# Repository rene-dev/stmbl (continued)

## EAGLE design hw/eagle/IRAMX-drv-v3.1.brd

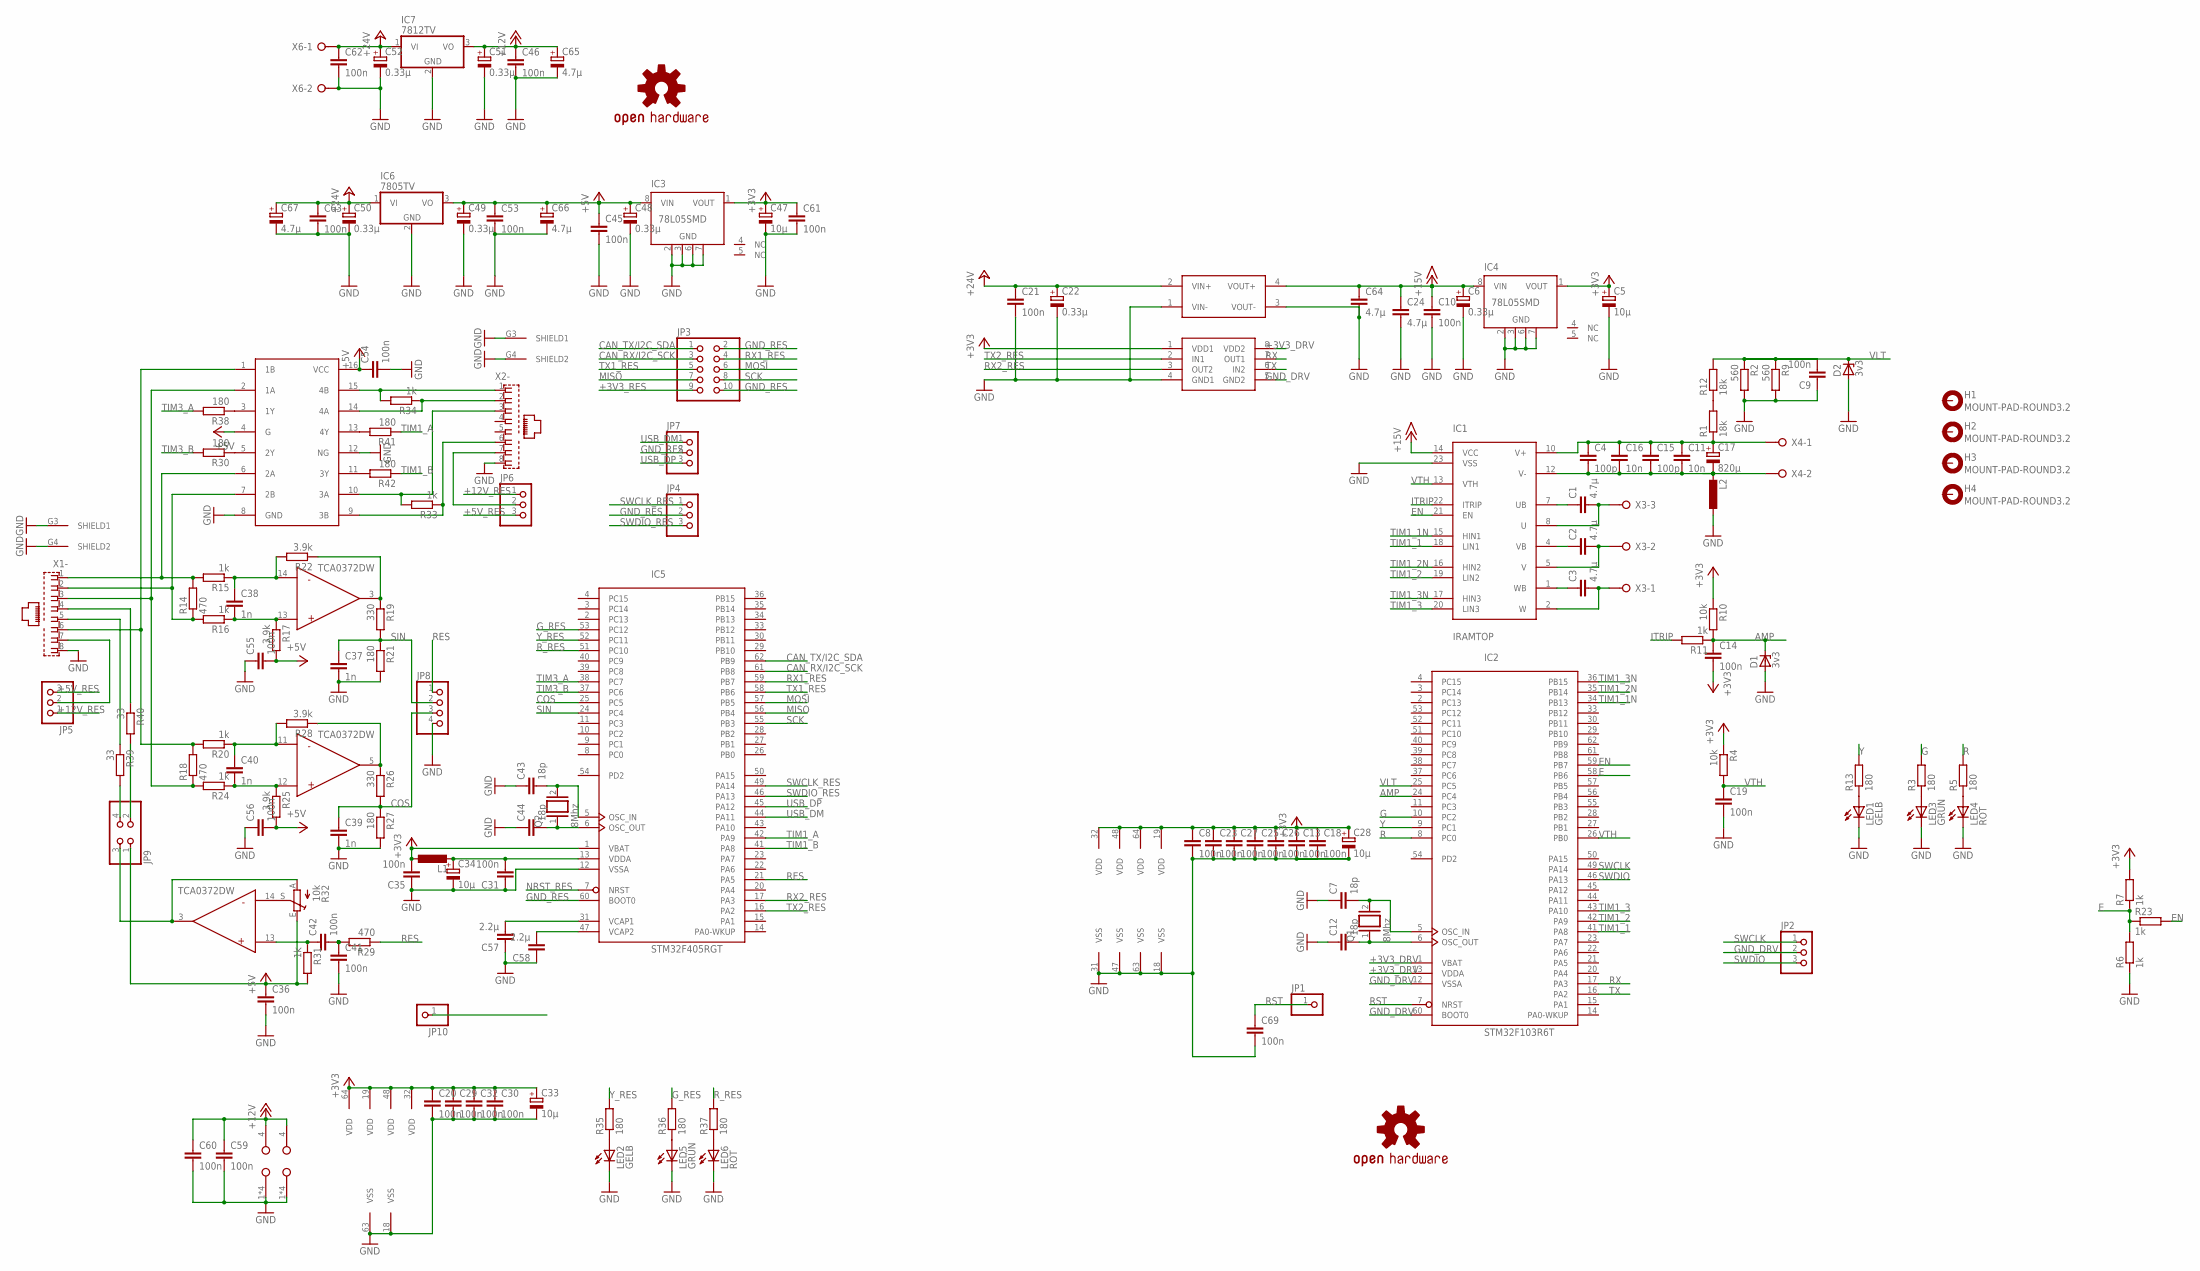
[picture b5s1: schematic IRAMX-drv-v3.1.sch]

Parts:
C1, C2, C3, C24, C64: 4.7µ; C0805K
C4, C15: 100p; C1206K
C5, C28, C33, C34, C47: 10µ; A/3216-18R
C6, C22, C48, C49, C50, C51, C52: 0.33µ; A/3216-18R
C7, C12, C43, C44: 18p; C0805
C8, C9, C10, C13, C14, C18, C19, C20, C21, C23, C25, C26, C27, C29, C30, C31, C32, C35, C36, C41, C42, C45, C46, C53, C54, C55, C56, C59, C60, C61, C62, C63, C69: 100n; C0805K
C11, C16: 10n; C0805K
C17: 820µ; EB35D
C37, C38, C39, C40: 1n; C0805K
C57, C58: 2.2µ; C0805K
C65, C66, C67: 4.7µ; E2,5-6
D1, D2: 3v3; SOD80C
H1, H2, H3, H4: MOUNT-PAD-ROUND3.2; 3,2-PAD
IC1: IRAMTOP; SIP23_TOP
IC2: STM32F103R6T; LQFP64
IC3, IC4: 78L05SMD; SO08
IC5: STM32F405RGT; LQFP64
IC6: 7805TV; TO220V
IC7: 7812TV; TO220V
JP1, JP10: PINHD-1X1; 1X01
JP2, JP4, JP5, JP6, JP7: PINHD-1X3; 1X03
JP3: PINHD-2X5; 2X05
JP8: PINHD-1X4; 1X04
JP9: PINHD-2X2; 2X02
L1, L2: L-EUL2825P; L2825P
LED1, LED2: GELB; LED3MM
LED3, LED5: GRÜN; LED3MM
LED4, LED6: ROT; LED3MM
LOGO1, LOGO2: OSHW-LOGOL; OSHW-LOGO-L
Q1, Q2: 8Mhz; QS
R1, R12: 18k; CER
R2, R9: 560; R0805
R3, R5, R13, R21, R27, R30, R35, R36, R37, R38, R41, R42: 180; R0805
R4, R10: 10k; R0805
R6, R7, R11, R15, R16, R20, R23, R24, R31, R33, R34: 1k; R0805
R14, R18, R29: 470; R0805
R17, R22, R25, R28: 3.9k; R0805
R19, R26: 330; R0805
R32: 10k; CA6V
R39, R40: 33; R0805
U$1: SI8621; SOIC08
U$2: RO-XXXX; SIP4
U$3, U$4: TCA0372DWDM2; TCA0372DM2
U$5: AM26LS32ACD; SO16
X1, X2: RJ45
X3: W237-03P; W237-133
X4, X6: W237-02P; W237-132

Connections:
+3V3_DRV: C5.+, C8.1, C13.1, C14.2, C18.1, C23.1, C25.1, C26.1, C27.1, C28.+, IC2.1 (VBAT), IC2.13 (VDDA), IC2.19 (VDD), IC2.32 (VDD), IC2.48 (VDD), IC2.64 (VDD), IC4.1 (VOUT), R4.1, R7.2, R10.1, U$1.8 (VDD2)
+3V3_RES: C20.1, C29.1, C30.1, C32.1, C33.+, C35.2, C47.+, C61.1, IC3.1 (VOUT), IC5.1 (VBAT), IC5.19 (VDD), IC5.32 (VDD), IC5.48 (VDD), IC5.64 (VDD), JP3.9, L1.1, U$1.1 (VDD1)
+5V_RES: C36.1, C45.1, C48.+, C49.+, C53.1, C54.1, C55.2, C56.2, C66.+, IC3.8 (VIN), IC6.3 (VO), JP5.3, JP6.3, JP9.1, R17.2, R25.2, R31.2, R32.E, U$5.4 (G), U$5.16 (VCC)
+12V_RES: C46.1, C51.+, C59.1, C60.1, C65.+, IC7.3 (VO), JP5.1, JP6.1, U$3.4 (VCC), U$4.4 (VCC)
+15V_DRV: C6.+, C10.1, C24.1, C64.1, IC1.14 (VCC), IC4.8 (VIN), U$2.4 (VOUT+)
+24V_RES: C21.1, C22.+, C50.+, C52.+, C62.1, C63.1, C67.+, IC6.1 (VI), IC7.1 (VI), U$2.2 (VIN+), X6.1
AMP: C14.1, D1.C, IC2.24 (PC4), R10.2, R11.1
CAN_RX/I2C_SCK: IC5.61 (PB8), JP3.3
CAN_TX/I2C_SDA: IC5.62 (PB9), JP3.1
COS: C39.1, IC5.25 (PC5), JP8.3, R26.2, R27.1
E: IC2.58 (PB6), R6.2, R7.1, R23.1
EN: IC1.21 (EN), IC2.59 (PB7), R23.2
G: IC2.10 (PC2), R3.2
GND_DRV: C5.-, C6.-, C7.1, C8.2, C9.1, C10.2, C12.1, C13.2, C18.2, C19.2, C23.2, C24.2, C25.2, C26.2, C27.2, C28.-, C64.2, C69.2, D1.A, D2.A, IC1.23 (VSS), IC2.12 (VSSA), IC2.18 (VSS), IC2.31 (VSS), IC2.47 (VSS), IC2.60 (BOOT0), IC2.63 (VSS), IC4.2 (GND), IC4.3 (GND), IC4.6 (GND), IC4.7 (GND), JP2.2, L2.1, LED1.K (C), LED3.K (C), LED4.K (C), R2.2, R6.1, R9.2, U$1.5 (GND2), U$2.3 (VOUT-)
GND_RES: C20.2, C21.2, C22.-, C29.2, C30.2, C31.1, C32.2, C33.-, C34.-, C35.1, C36.2, C37.2, C39.2, C41.2, C43.1, C44.1, C45.2, C46.2, C47.-, C48.-, C49.-, C50.-, C51.-, C52.-, C53.2, C54.2, C55.1, C56.1, C57.1, C58.1, C59.2, C60.2, C61.2, C62.2, C63.2, C65.-, C66.-, C67.-, IC3.2 (GND), IC3.3 (GND), IC3.6 (GND), IC3.7 (GND), IC5.12 (VSSA), IC5.18 (VSS), IC5.60 (BOOT0), IC5.63 (VSS), IC6.2 (GND), IC7.2 (GND), JP3.2, JP3.10, JP4.2, JP7.2, JP8.4, LED2.K (C), LED5.K (C), LED6.K (C), R21.2, R27.2, U$1.4 (GND1), U$2.1 (VIN-), U$3.1 (GND), U$3.8 (GND), U$3.9 (GND), U$3.16 (GND), U$4.1 (GND), U$4.8 (GND), U$4.9 (GND), U$4.16 (GND), U$5.8 (GND), U$5.12 (NG), X1.8, X1.G3 (SHIELD1), X1.G4 (SHIELD2), X2.8, X2.G3 (SHIELD1), X2.G4 (SHIELD2), X6.2
G_RES: IC5.53 (PC12), R36.2
ITRIP: IC1.22 (ITRIP), R11.2
MISO: IC5.56 (PB4), JP3.7
MOSI: IC5.57 (PB5), JP3.6
unnamed: C1.1, IC1.7 (UB)
unnamed: R1.P$2 (2), R12.P$1 (1)
unnamed: C2.1, IC1.4 (VB)
unnamed: LED2.A, R35.1
unnamed: C3.1, IC1.1 (WB)
unnamed: R32.S, U$4.14 (IN-)
unnamed: LED3.A, R3.1
unnamed: LED4.A, R5.1
unnamed: C7.2, IC2.5 (OSC_IN), Q1.2
unnamed: LED5.A, R36.1
unnamed: C12.2, IC2.6 (OSC_OUT), Q1.1
unnamed: C58.2, IC5.47 (VCAP2)
unnamed: C57.2, IC5.31 (VCAP1)
unnamed: C44.2, IC5.6 (OSC_OUT), Q2.1
unnamed: JP5.2, X1.7
unnamed: JP9.4, R39.2
unnamed: R19.1, R22.1, U$3.3 (OUT)
unnamed: C38.2, R16.1, R17.1, U$3.13 (IN+)
unnamed: LED6.A, R37.1
unnamed: JP9.2, R40.2
unnamed: C40.2, R24.1, R25.1, U$3.12 (IN+)
unnamed: JP6.2, X2.7
unnamed: R26.1, R28.1, U$3.5 (OUT)
unnamed: R40.1, X1.4
unnamed: C40.1, R20.1, R28.2, U$3.11 (IN-)
unnamed: R34.2, U$5.15 (4B), X2.1
unnamed: C41.1, C42.2, R29.2
unnamed: C42.1, R31.1, U$4.13 (IN+)
unnamed: C38.1, R15.1, R22.2, U$3.14 (IN-)
unnamed: JP9.3, R32.A, U$4.3 (OUT)
unnamed: R39.1, X1.5
unnamed: R30.1, U$5.5 (2Y)
unnamed: R34.1, U$5.14 (4A), X2.2
unnamed: R33.2, U$5.10 (3A), X2.3
unnamed: R33.1, U$5.9 (3B), X2.6
unnamed: C43.2, IC5.5 (OSC_IN), Q2.2
unnamed: R18.2, R20.2, U$5.1 (1B), X1.6
unnamed: R14.1, R16.2, U$5.7 (2B), X1.2
unnamed: R42.2, U$5.11 (3Y)
unnamed: LED1.A, R13.1
unnamed: R41.2, U$5.13 (4Y)
unnamed: R38.1, U$5.3 (1Y)
unnamed: C31.2, C34.+, IC5.13 (VDDA), L1.2
unnamed: R14.2, R15.2, U$5.6 (2A), X1.1
unnamed: R18.1, R24.2, U$5.2 (1A), X1.3
NRST_RES: IC5.7 (NRST), JP10.1
R: IC2.8 (PC0), R5.2
RES: IC5.21 (PA5), JP8.1, R29.1
RST: C69.1, IC2.7 (NRST), JP1.1
RX: IC2.17 (PA3), U$1.7 (OUT1)
RX1_RES: IC5.59 (PB7), JP3.4
RX2_RES: IC5.17 (PA3), U$1.3 (OUT2)
R_RES: IC5.51 (PC10), R37.2
SCK: IC5.55 (PB3), JP3.8
SIN: C37.1, IC5.24 (PC4), JP8.2, R19.2, R21.1
SWCLK: IC2.49 (PA14), JP2.1
SWCLK_RES: IC5.49 (PA14), JP4.1
SWDIO: IC2.46 (PA13), JP2.3
SWDIO_RES: IC5.46 (PA13), JP4.3
TIM1_1: IC1.18 (LIN1), IC2.41 (PA8)
TIM1_1N: IC1.15 (HIN1), IC2.34 (PB13)
TIM1_2: IC1.19 (LIN2), IC2.42 (PA9)
TIM1_2N: IC1.16 (HIN2), IC2.35 (PB14)
TIM1_3: IC1.20 (LIN3), IC2.43 (PA10)
TIM1_3N: IC1.17 (HIN3), IC2.36 (PB15)
TIM1_A: IC5.42 (PA9), R41.1
TIM1_B: IC5.41 (PA8), R42.1
TIM3_A: IC5.38 (PC7), R38.2
TIM3_B: IC5.37 (PC6), R30.2
TX: IC2.16 (PA2), U$1.6 (IN2)
TX1_RES: IC5.58 (PB6), JP3.5
TX2_RES: IC5.16 (PA2), U$1.2 (IN1)
U: C1.2, IC1.8 (U), X3.3
USB_DM: IC5.44 (PA11), JP7.1
USB_DP: IC5.45 (PA12), JP7.3
V: C2.2, IC1.5 (V), X3.2
V+: C4.1, C11.1, C15.1, C16.1, C17.+, IC1.10 (V+), R1.P$1 (1), X4.1
V-: C4.2, C11.2, C15.2, C16.2, C17.-, IC1.12 (V-), L2.2, X4.2
VLT: C9.2, D2.C, IC2.25 (PC5), R2.1, R9.1, R12.P$2 (2)
VTH: C19.1, IC1.13 (VTH), IC2.26 (PB0), R4.2
W: C3.2, IC1.2 (W), X3.1
Y: IC2.9 (PC1), R13.2
Y_RES: IC5.52 (PC11), R35.2

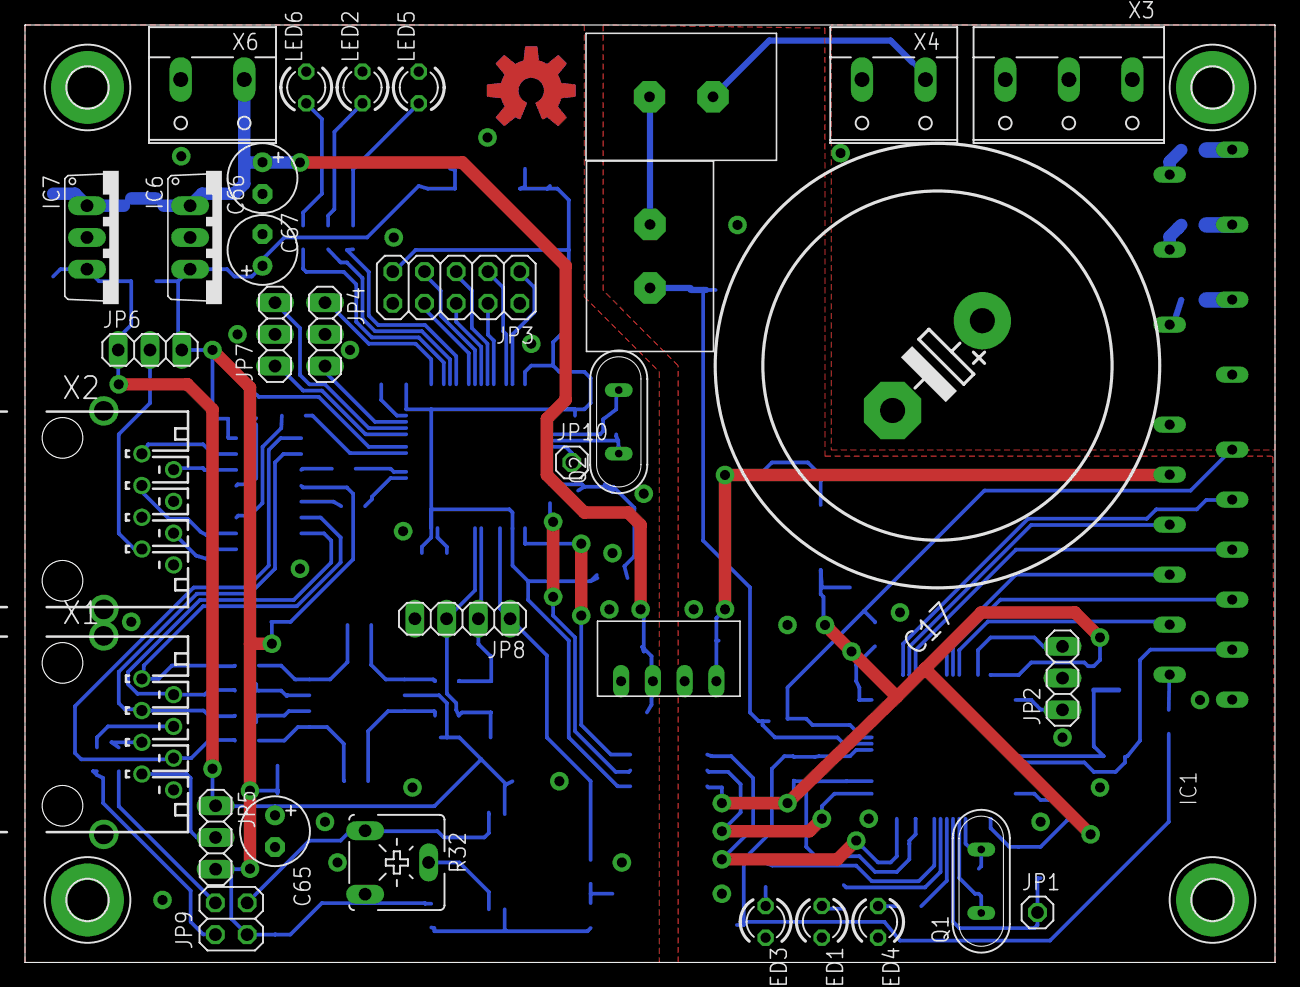
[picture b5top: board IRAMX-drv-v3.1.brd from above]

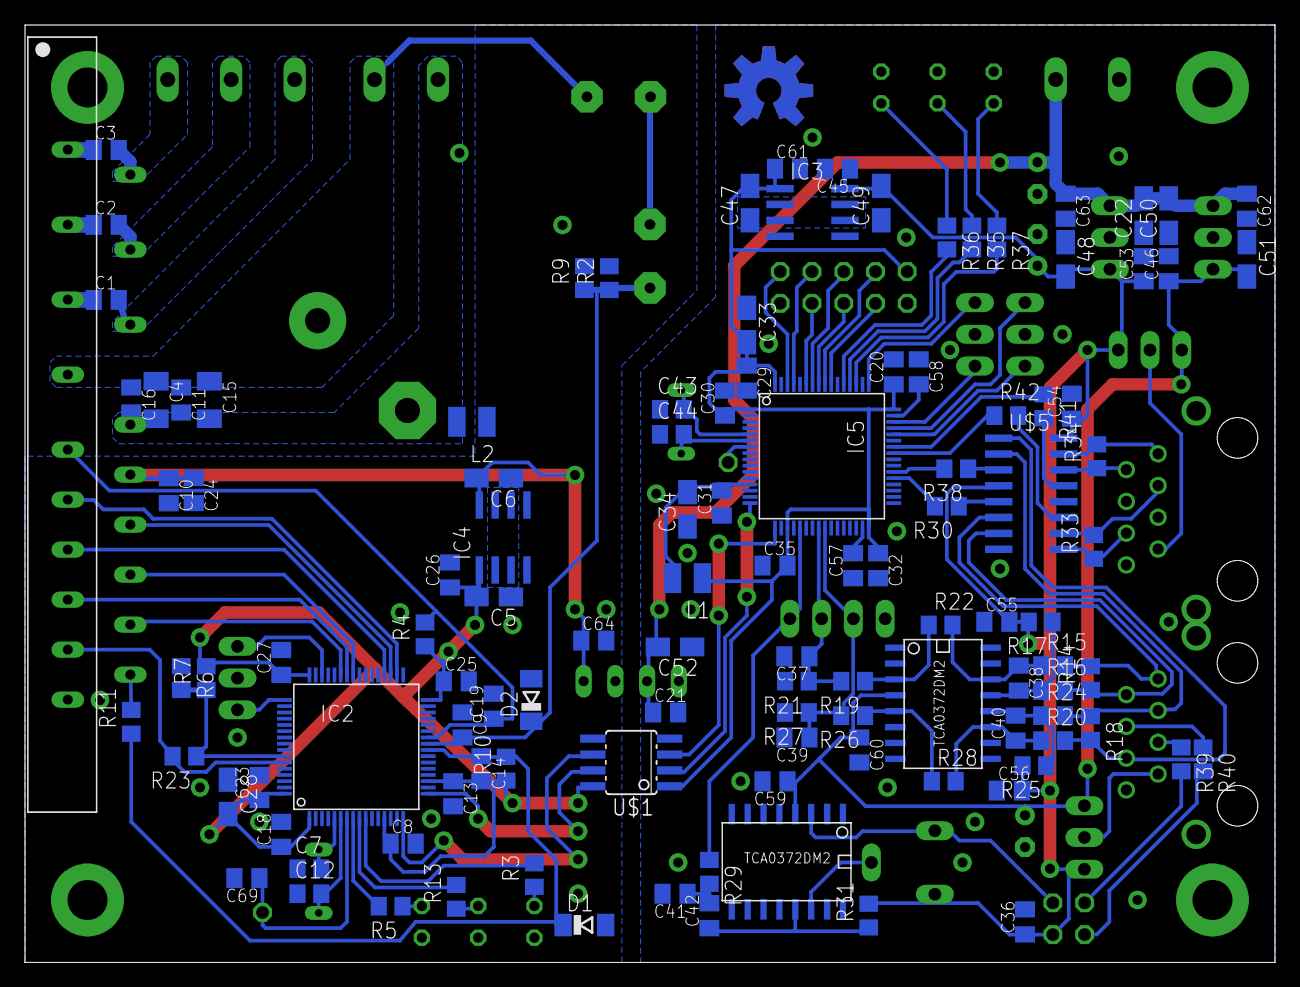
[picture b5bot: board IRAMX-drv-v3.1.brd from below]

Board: 2 copper layers, 100.0 x 75.0 mm, 154 parts (115 on the bottom side), 102 nets.

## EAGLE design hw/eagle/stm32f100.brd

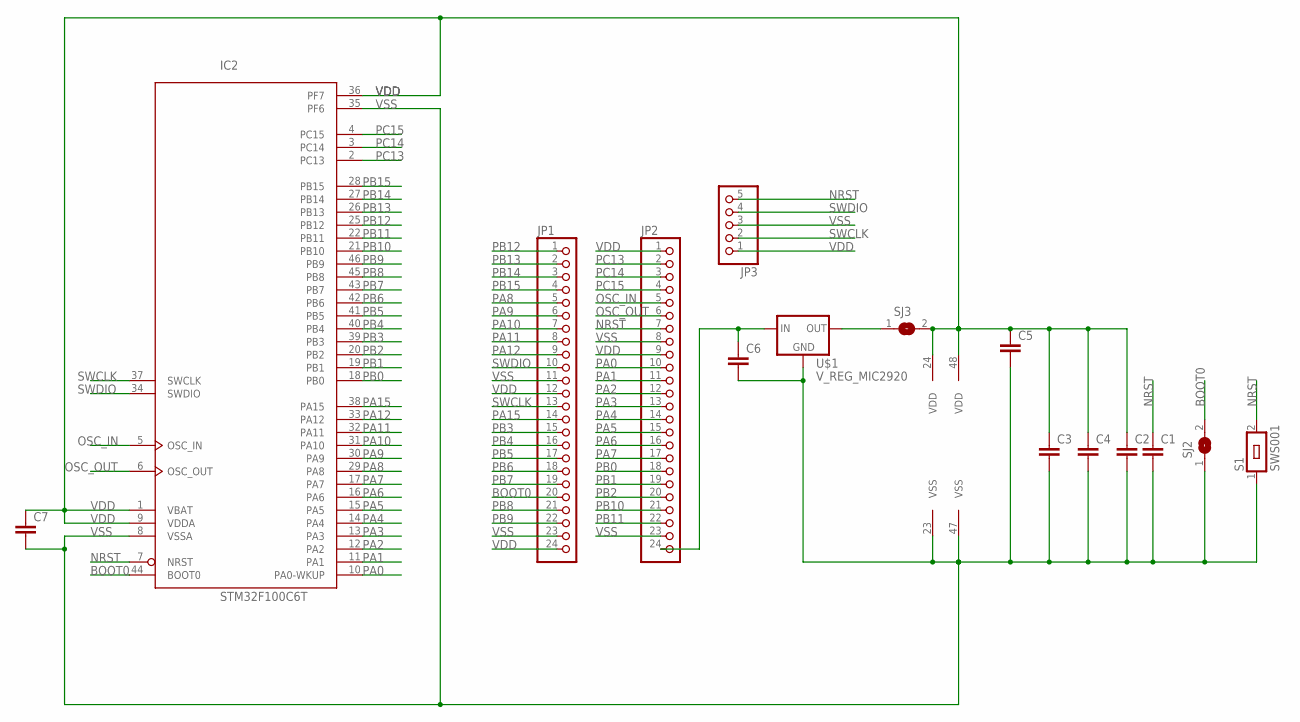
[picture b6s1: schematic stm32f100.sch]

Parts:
C1, C2, C3, C4, C7: C-EUC0603K; C0603K
C5, C6: C-EUC1210K; C1210K
IC2: STM32F100C6T; LQFP48
JP1, JP2: PINHD-1X24; 1X24
JP3: PINHD-1X5; 1X05
S1: SWS001; SMS-001
SJ2, SJ3: SJ
U$1: V_REG_MIC2920; SOT223

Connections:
BOOT0: IC2.44 (BOOT0), JP1.20, SJ2.2
unnamed: SJ3.1, U$1.2 (OUT), U$1.4 (OUT)
unnamed: C6.1, JP2.24, U$1.3 (IN)
NRST: C1.1, IC2.7 (NRST), JP2.7, JP3.5, S1.2
OSC_IN: IC2.5 (OSC_IN), JP2.5
OSC_OUT: IC2.6 (OSC_OUT), JP2.6
PA0: IC2.10 (PA0-WKUP), JP2.10
PA1: IC2.11 (PA1), JP2.11
PA2: IC2.12 (PA2), JP2.12
PA3: IC2.13 (PA3), JP2.13
PA4: IC2.14 (PA4), JP2.14
PA5: IC2.15 (PA5), JP2.15
PA6: IC2.16 (PA6), JP2.16
PA7: IC2.17 (PA7), JP2.17
PA8: IC2.29 (PA8), JP1.5
PA9: IC2.30 (PA9), JP1.6
PA10: IC2.31 (PA10), JP1.7
PA11: IC2.32 (PA11), JP1.8
PA12: IC2.33 (PA12), JP1.9
PA15: IC2.38 (PA15), JP1.14
PB0: IC2.18 (PB0), JP2.18
PB1: IC2.19 (PB1), JP2.19
PB2: IC2.20 (PB2), JP2.20
PB3: IC2.39 (PB3), JP1.15
PB4: IC2.40 (PB4), JP1.16
PB5: IC2.41 (PB5), JP1.17
PB6: IC2.42 (PB6), JP1.18
PB7: IC2.43 (PB7), JP1.19
PB8: IC2.45 (PB8), JP1.21
PB9: IC2.46 (PB9), JP1.22
PB10: IC2.21 (PB10), JP2.21
PB11: IC2.22 (PB11), JP2.22
PB12: IC2.25 (PB12), JP1.1
PB13: IC2.26 (PB13), JP1.2
PB14: IC2.27 (PB14), JP1.3
PB15: IC2.28 (PB15), JP1.4
PC13: IC2.2 (PC13), JP2.2
PC14: IC2.3 (PC14), JP2.3
PC15: IC2.4 (PC15), JP2.4
SWCLK: IC2.37 (SWCLK), JP1.13, JP3.2
SWDIO: IC2.34 (SWDIO), JP1.10, JP3.4
VDD: C2.1, C3.1, C4.1, C5.1, C7.1, IC2.1 (VBAT), IC2.9 (VDDA), IC2.24 (VDD), IC2.36 (PF7), IC2.48 (VDD), JP1.12, JP1.24, JP2.1, JP2.9, JP3.1, SJ3.2
VSS: C1.2, C2.2, C3.2, C4.2, C5.2, C6.2, C7.2, IC2.8 (VSSA), IC2.23 (VSS), IC2.35 (PF6), IC2.47 (VSS), JP1.11, JP1.23, JP2.8, JP2.23, JP3.3, S1.1, SJ2.1, U$1.1 (GND)

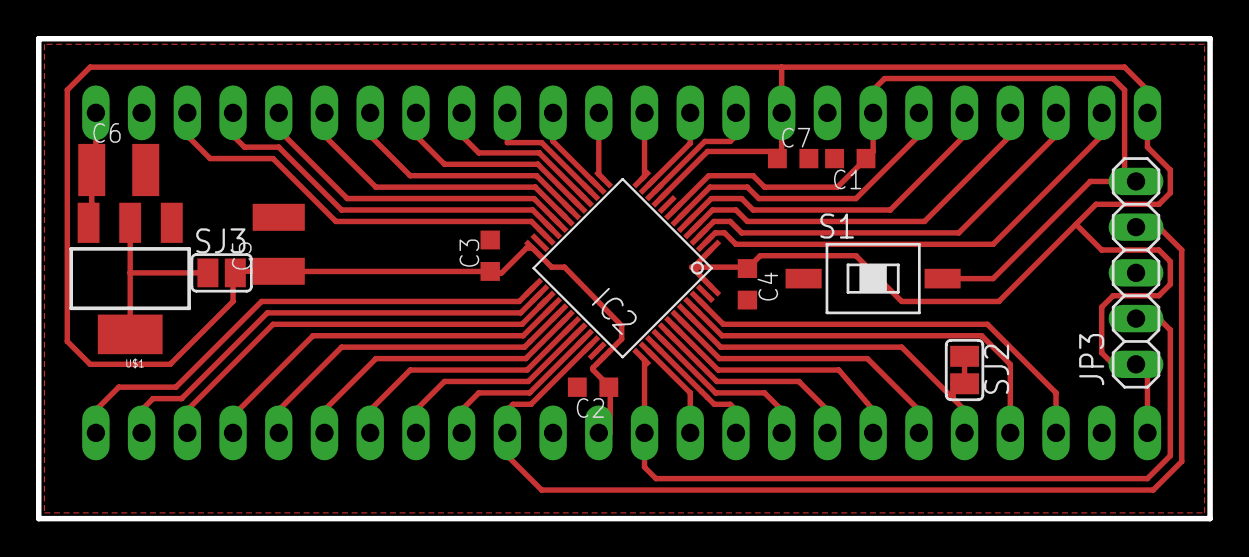
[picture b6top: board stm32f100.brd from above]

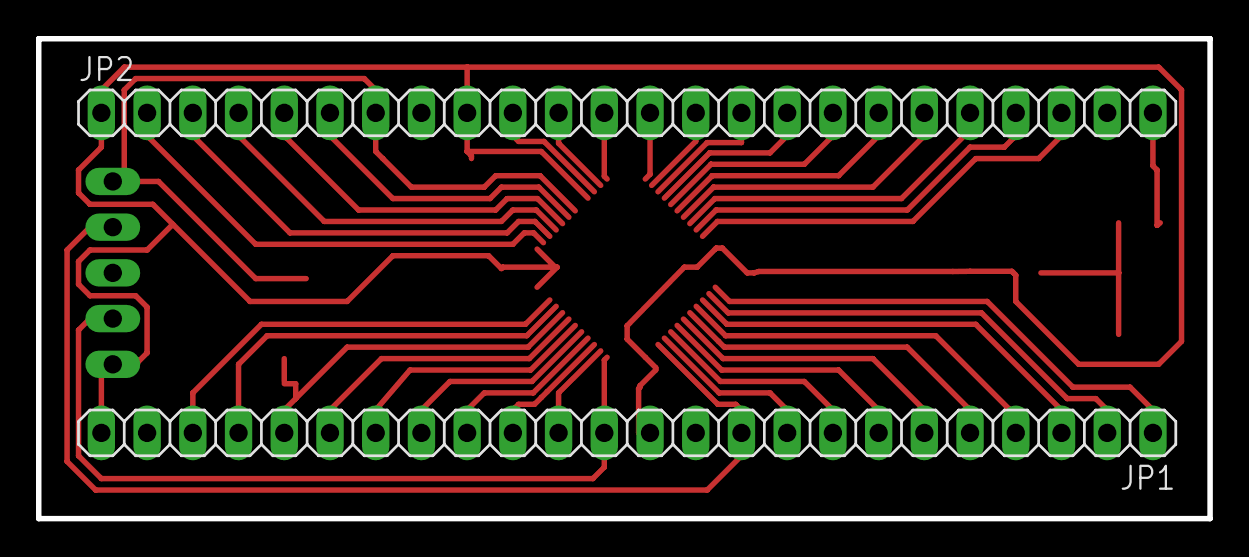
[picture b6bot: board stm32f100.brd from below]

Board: 2 copper layers, 65.1 x 26.7 mm, 15 parts (2 on the bottom side), 43 nets.

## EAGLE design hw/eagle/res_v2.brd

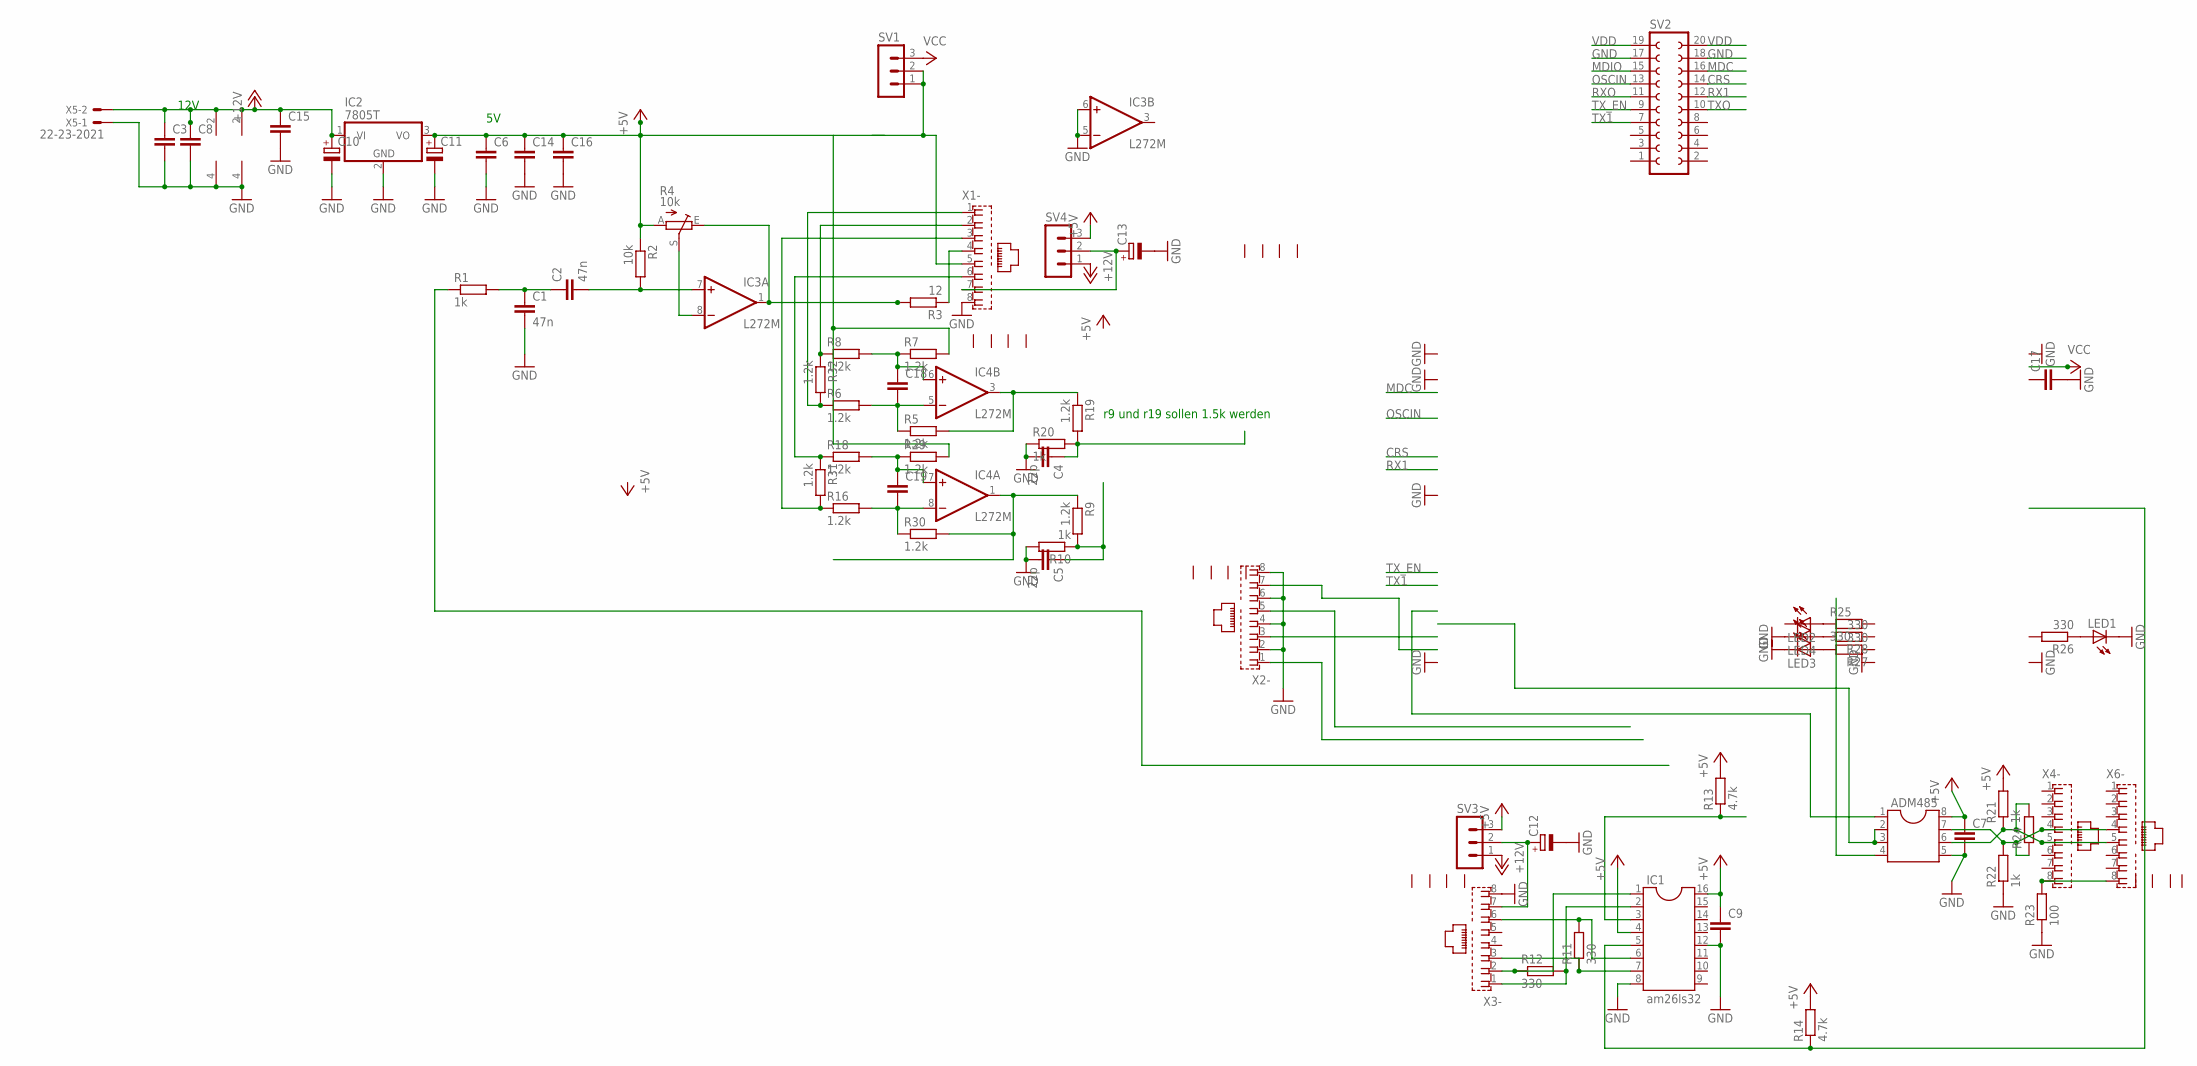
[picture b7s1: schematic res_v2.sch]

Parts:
ADM485: DIL8; DIL08
C1, C2: 47n; C050-025X075
C3, C6, C7, C8, C9, C14, C15, C16, C17, C18, C19: C-EU050-025X075; C050-025X075
C4, C5: 22p; C050-025X075
C10, C11, C12, C13: CPOL-EUE2.5-5; E2,5-5
IC1: am26ls32; DIL16
IC2: 7805T; TO220H
IC3, IC4: L272M; DIL08
LED1, LED2, LED3, LED4: LED3MM
R1, R10, R20, R21, R22: 1k; 0204/7
R2: 10k; 0204/7
R3: 12; 0204/7
R4: 10k; CA6V
R5, R6, R7, R8, R9, R16, R18, R19, R29, R30, R31, R32: 1.2k; 0204/7
R11, R12, R25, R26, R27, R28: 330; 0204/7
R13, R14: 4.7k; 0204/7
R23: 100; 0204/7
R24: R-EU_0204/7; 0204/7
SV1, SV3, SV4: MA03-1
SV2: FE10-2W
X1, X2, X3, X4, X6: RJ45
X5: 22-23-2021

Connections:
+5V: ADM485.8, C6.1, C7.1, C9.1, C11.+, C14.1, C16.1, IC1.4, IC1.16, IC2.3 (VO), R2.1, R4.A, R7.2, R13.2, R14.2, R21.2, R29.2, SV3.3, SV4.3
+12V: C3.1, C8.1, C10.+, C15.1, IC2.1 (VI), IC3.2 (V+), IC4.2 (V+), SV3.1, SV4.1, X5.2
CRS: SV2.14
GND: ADM485.5, C1.2, C3.2, C4.2, C5.2, C6.2, C7.2, C8.2, C9.2, C10.-, C11.-, C12.-, C13.-, C14.2, C15.2, C16.2, C17.2, IC1.8, IC1.12, IC2.2 (GND), IC3.4 (GND), IC3.5 (-IN), IC3.6 (+IN), IC4.4 (GND), LED1.K (C), LED3.K (C), LED4.K (C), R10.2, R20.1, R22.1, R23.1, SV2.17, SV2.18, X1.8, X2.2, X2.4, X2.6, X2.8, X3.8, X5.1
MDC: SV2.16
MDIO: SV2.15
unnamed: IC3.8 (-IN), R4.S
unnamed: IC3.1 (OUT), R3.2, R4.E
unnamed: C2.2, IC3.7 (+IN), R2.2
unnamed: C1.1, C2.1, R1.2
unnamed: R3.1, X1.4
unnamed: R8.1, R32.1, X1.2
unnamed: R6.1, R32.2, X1.1
unnamed: C18.2, IC4.5 (-IN), R5.1, R6.2
unnamed: C18.1, IC4.6 (+IN), R7.1, R8.2
unnamed: IC4.3 (OUT), R5.2, R19.1
unnamed: IC4.1 (OUT), R9.1, R30.2
unnamed: C12.+, SV3.2, X3.7
unnamed: IC1.6, R11.2, X3.6
unnamed: C4.1, R19.2, R20.2
unnamed: R16.1, R31.2, X1.3
unnamed: IC1.3, R13.1
unnamed: IC1.5, R14.1
unnamed: IC1.2, R12.2, X3.1
unnamed: IC1.1, R12.1, X3.2
unnamed: IC1.7, R11.1, X3.3
unnamed: C13.+, SV4.2, X1.7
unnamed: C19.1, IC4.7 (+IN), R18.2, R29.1
unnamed: SV1.1, SV1.2, X1.5
unnamed: R18.1, R31.1, X1.6
unnamed: C19.2, IC4.8 (-IN), R16.2, R30.1
unnamed: C5.1, R9.2, R10.1
unnamed: ADM485.2, ADM485.3
unnamed: ADM485.6, R21.1, R24.2, X4.5, X6.5
unnamed: ADM485.7, R22.2, R24.1, X4.4, X6.4
unnamed: R23.2, X4.8, X6.8
unnamed: LED2.A, R25.1
unnamed: LED1.A, R26.1
unnamed: LED3.A, R27.2
unnamed: LED4.A, R28.2
OSCIN: SV2.13
RX1: SV2.12
RXO: SV2.11
TX1: SV2.7
TXO: SV2.10
TX_EN: SV2.9
VCC: SV1.3
VDD: SV2.19, SV2.20

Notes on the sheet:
12V
r9 und r19 sollen 1.5k werden

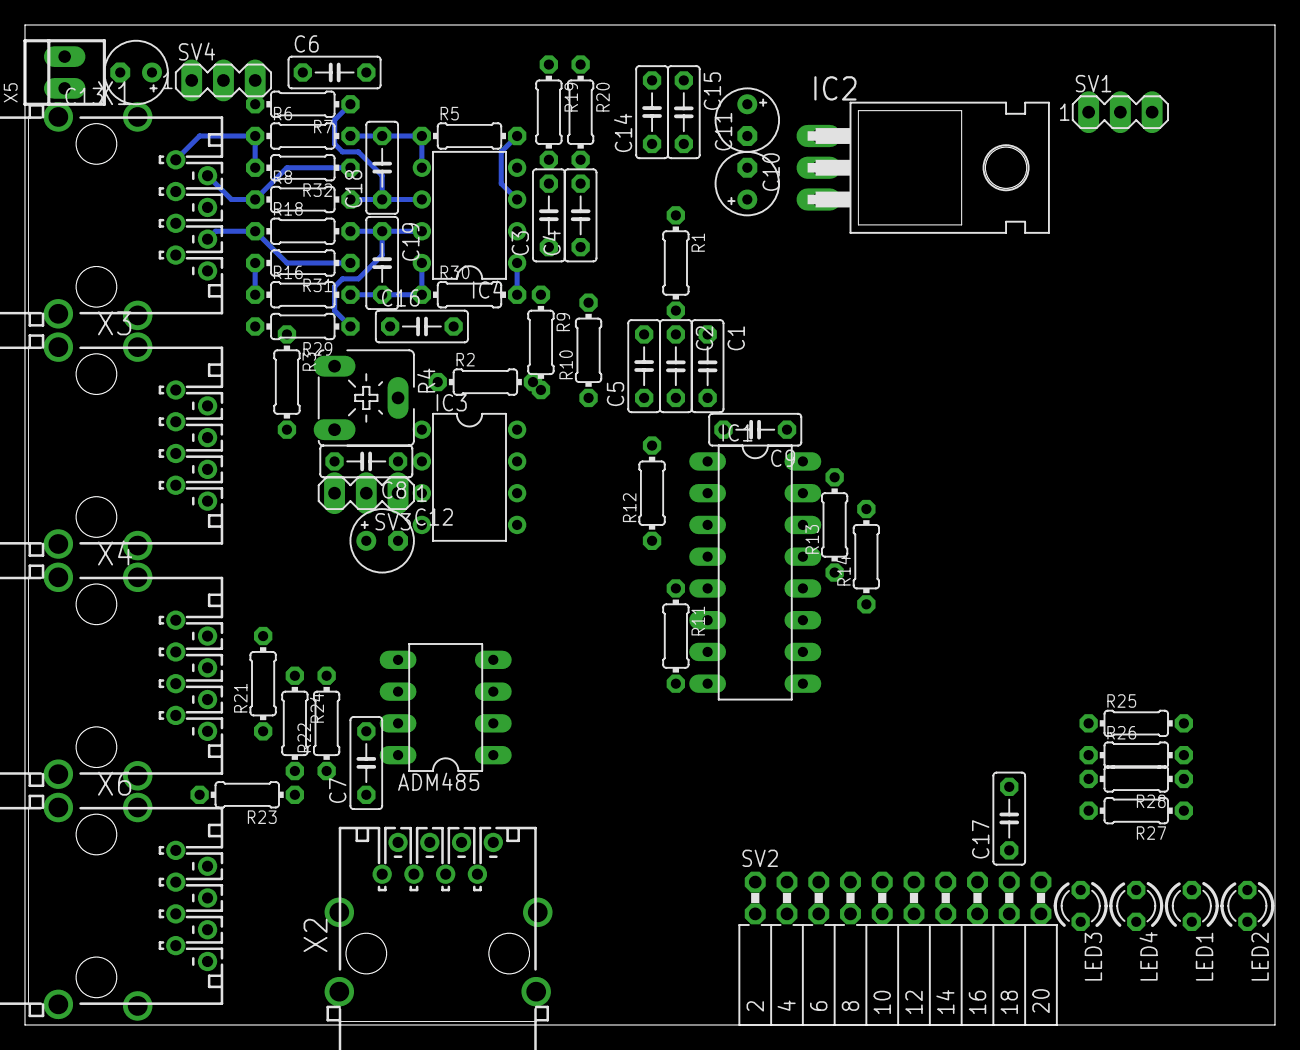
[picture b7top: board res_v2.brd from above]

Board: 2 copper layers, 100.0 x 80.0 mm, 68 parts (0 on the bottom side), 38 nets.

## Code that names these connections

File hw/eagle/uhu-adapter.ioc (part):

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Mcu.Name=STM32F303C(B-C)Tx
Mcu.Package=LQFP48
Mcu.UserName=STM32F303CBTx
PA10.Mode=Activate-Break-Input
PA10.Signal=TIM8_BKIN
PA11.Mode=Device
PA11.Signal=USB_DM
PA12.Mode=Device
PA12.Signal=USB_DP
PA13.Mode=Serial_Wire
PA13.Signal=SYS_JTMS-SWDIO
PA14.Mode=Serial_Wire
PA14.Signal=SYS_JTCK-SWCLK
PB10.Mode=Asynchronous
PB10.Signal=USART3_TX
PB11.Mode=Asynchronous
PB11.Signal=USART3_RX
PB12.Signal=TIM1_BKIN
PB3.GPIOParameters=GPIO_Label
PB3.GPIO_Label=ERROR
PB3.Signal=GPIO_Output
PB4.Signal=S_TIM3_CH1
PB5.Signal=S_TIM3_CH2
PB6.Signal=S_TIM4_CH1
PB7.Signal=S_TIM4_CH2
PB8.Signal=S_TIM8_CH2
PB9.Signal=S_TIM8_CH3
PF0-OSC_IN.Mode=HSE-External-Oscillator
PF0-OSC_IN.Signal=RCC_OSC_IN
PF1-OSC_OUT.Mode=HSE-External-Oscillator
PF1-OSC_OUT.Signal=RCC_OSC_OUT
RCC.HSEPLLFreq_Value=24000000
RCC.HSE_VALUE=24000000
RCC.SYSCLKFreq_VALUE=72000000
RCC.SYSCLKSourceVirtual=RCC_SYSCLKSOURCE_PLLCLK

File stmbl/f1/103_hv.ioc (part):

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Mcu.Name=STM32F103R(4-6)Tx
Mcu.Package=LQFP64
Mcu.UserName=STM32F103R6Tx
PA10.Signal=S_TIM1_CH3
PA13.Mode=Serial_Wire
PA13.Signal=SYS_JTMS-SWDIO
PA14.Mode=Serial_Wire
PA14.Signal=SYS_JTCK-SWCLK
PA2.Mode=Asynchronous
PA2.Signal=USART2_TX
PA3.Mode=Asynchronous
PA3.Signal=USART2_RX
PA8.Signal=S_TIM1_CH1
PA9.Signal=S_TIM1_CH2
PB0.Signal=ADCx_IN8
PB13.Mode=Output Compare1 CH1 CH1N
PB13.Signal=TIM1_CH1N
PB14.Mode=Output Compare2 CH2 CH2N
PB14.Signal=TIM1_CH2N
PB15.Mode=Output Compare3 CH3 CH3N
PB15.Signal=TIM1_CH3N
PB6.Signal=GPIO_Output
PB7.Signal=GPIO_Input
PC0.Signal=GPIO_Output
PC1.Signal=GPIO_Output
PC2.Signal=GPIO_Output
PC4.Signal=ADCx_IN14
PC5.Signal=ADCx_IN15
PD0-OSC_IN.Mode=HSE-External-Oscillator
PD0-OSC_IN.Signal=RCC_OSC_IN
PD1-OSC_OUT.Mode=HSE-External-Oscillator
PD1-OSC_OUT.Signal=RCC_OSC_OUT
RCC.SYSCLKFreq_VALUE=72000000
RCC.SYSCLKSource=RCC_SYSCLKSOURCE_PLLCLK

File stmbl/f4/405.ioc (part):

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Mcu.Name=STM32F405RGTx
Mcu.Package=LQFP64
Mcu.UserName=STM32F405RGTx
PA11.Mode=Device_Only
PA11.Signal=USB_OTG_FS_DM
PA12.Mode=Device_Only
PA12.Signal=USB_OTG_FS_DP
PA13.Mode=Serial_Wire
PA13.Signal=SYS_JTMS-SWDIO
PA14.Mode=Serial_Wire
PA14.Signal=SYS_JTCK-SWCLK
PA2.Mode=Asynchronous
PA2.Signal=USART2_TX
PA3.Mode=Asynchronous
PA3.Signal=USART2_RX
PA8.Signal=S_TIM1_CH1
PA9.Signal=S_TIM1_CH2
PB10.Mode=Asynchronous
PB10.Signal=USART3_TX
PB11.Mode=Asynchronous
PB11.Signal=USART3_RX
PC12.Mode=Asynchronous
PC12.Signal=UART5_TX
PC4.Signal=ADCx_IN14
PC5.Signal=ADCx_IN15
PC6.Signal=S_TIM3_CH1
PC7.Signal=S_TIM3_CH2
PD2.Mode=Asynchronous
PD2.Signal=UART5_RX
PH0-OSC_IN.Mode=HSE-External-Oscillator
PH0-OSC_IN.Signal=RCC_OSC_IN
PH1-OSC_OUT.Mode=HSE-External-Oscillator
PH1-OSC_OUT.Signal=RCC_OSC_OUT
RCC.HSE_VALUE=8000000
RCC.SYSCLKFreq_VALUE=168000000
RCC.SYSCLKSource=RCC_SYSCLKSOURCE_PLLCLK

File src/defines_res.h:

// defines für stm32f405

// resolver
//// adc
#define SIN_ADC ADC1
#define SIN_ADC_RCC RCC_APB2Periph_ADC1
#define SIN_ADC_CHAN ADC_Channel_14

#define COS_ADC ADC2
#define COS_ADC_RCC RCC_APB2Periph_ADC2
#define COS_ADC_CHAN ADC_Channel_15

//// timer
#define RES_TIM TIM2
#define RES_TIM_RCC RCC_APB1Periph_TIM2

//// dma
#define DMA DMA2_Stream2
#define DMA_RCC RCC_AHB1Periph_DMA2
#define DMA_CHAN DMA_Channel_1
#define DMA_IRQN DMA2_Stream2_IRQn

//// gpio
#define SIN_PIN GPIO_Pin_4
#define SIN_PORT GPIOC
#define SIN_IO_RCC RCC_AHB1Periph_GPIOC

#define COS_PIN GPIO_Pin_5
#define COS_PORT GPIOC
#define COS_IO_RCC RCC_AHB1Periph_GPIOC

#define RES_PIN GPIO_Pin_5
#define RES_PORT GPIOA
#define RES_IO_RCC RCC_AHB1Periph_GPIOA


// encoder
//// timer
#define ENC0_TIM TIM1
#define ENC0_TIM_RCC RCC_APB2Periph_TIM1

#define ENC1_TIM TIM3
#define ENC1_TIM_RCC RCC_APB1Periph_TIM3

//// gpio
#define ENC0_A_PIN GPIO_Pin_8
#define ENC0_A_PORT GPIOA
#define ENC0_A_IO_RCC RCC_AHB1Periph_GPIOA
#define ENC0_A_PIN_SOURCE GPIO_PinSource8
#define ENC0_A_AF_SOURCE GPIO_AF_TIM1


#define ENC0_B_PIN GPIO_Pin_9
#define ENC0_B_PORT GPIOA
#define ENC0_B_IO_RCC RCC_AHB1Periph_GPIOA
#define ENC0_B_PIN_SOURCE GPIO_PinSource9
#define ENC0_B_AF_SOURCE GPIO_AF_TIM1

#define ENC1_A_PIN GPIO_Pin_6
#define ENC1_A_PORT GPIOC
#define ENC1_A_IO_RCC RCC_AHB1Periph_GPIOC
#define ENC1_A_PIN_SOURCE GPIO_PinSource6
#define ENC1_A_AF_SOURCE GPIO_AF_TIM3

#define ENC1_B_PIN GPIO_Pin_7
#define ENC1_B_PORT GPIOC
#define ENC1_B_IO_RCC RCC_AHB1Periph_GPIOC
#define ENC1_B_PIN_SOURCE GPIO_PinSource7
#define ENC1_B_AF_SOURCE GPIO_AF_TIM3

// leds
#define LED_R_PIN GPIO_Pin_10
#define LED_R_PORT GPIOC
#define LED_R_IO_RCC RCC_AHB1Periph_GPIOC

#define LED_G_PIN GPIO_Pin_11
#define LED_G_PORT GPIOC
#define LED_G_IO_RCC RCC_AHB1Periph_GPIOC

// brake
#define BRAKE_PIN GPIO_Pin_9
#define BRAKE_PORT GPIOC
#define BRAKE_IO_RCC RCC_AHB1Periph_GPIOC

// fan
#define FAN_PIN GPIO_Pin_8
#define FAN_PORT GPIOC
#define FAN_IO_RCC RCC_AHB1Periph_GPIOC

#ifdef TROLLER

#define UART_DRV USART1
#define UART_DRV_RCC RCC_APB2Periph_USART1
#define UART_DRV_CLOCK_COMMAND RCC_APB2PeriphClockCmd

#define UART_DRV_RX_DMA DMA2_Stream5
#define UART_DRV_RX_DMA_RCC RCC_AHB1Periph_DMA2
#define UART_DRV_RX_DMA_CHAN DMA_Channel_4
#define UART_DRV_RX_DMA_IRQN DMA1_Stream5_IRQn
#define UART_DRV_RX_DMA_TCIF DMA_FLAG_TCIF5

#define UART_DRV_IRQ USART1_IRQHandler
#define UART_DRV_IRQN USART1_IRQn

#define UART_DRV_TX_DMA DMA2_Stream7
#define UART_DRV_TX_DMA_RCC RCC_AHB1Periph_DMA2
#define UART_DRV_TX_DMA_CHAN DMA_Channel_4
#define UART_DRV_TX_DMA_IRQN DMA1_Stream7_IRQn
#define UART_DRV_TX_DMA_TCIF DMA_FLAG_TCIF7

#define UART_DRV_RX_PIN GPIO_Pin_7
#define UART_DRV_RX_PORT GPIOB
#define UART_DRV_RX_IO_RCC RCC_AHB1Periph_GPIOB
#define UART_DRV_RX_PIN_SOURCE GPIO_PinSource7
#define UART_DRV_RX_AF_SOURCE GPIO_AF_USART1

#define UART_DRV_TX_PIN GPIO_Pin_6
#define UART_DRV_TX_PORT GPIOB
#define UART_DRV_TX_IO_RCC RCC_AHB1Periph_GPIOB
#define UART_DRV_TX_PIN_SOURCE GPIO_PinSource6
#define UART_DRV_TX_AF_SOURCE GPIO_AF_USART1

#else

#define UART_DRV USART2
#define UART_DRV_RCC RCC_APB1Periph_USART2
#define UART_DRV_CLOCK_COMMAND RCC_APB1PeriphClockCmd

#define UART_DRV_RX_DMA DMA1_Stream5
#define UART_DRV_RX_DMA_RCC RCC_AHB1Periph_DMA1
#define UART_DRV_RX_DMA_CHAN DMA_Channel_4
#define UART_DRV_RX_DMA_IRQN DMA1_Stream5_IRQn
#define UART_DRV_RX_DMA_TCIF DMA_FLAG_TCIF5

#define UART_DRV_IRQ USART2_IRQHandler
#define UART_DRV_IRQN USART2_IRQn

#define UART_DRV_TX_DMA DMA1_Stream6
#define UART_DRV_TX_DMA_RCC RCC_AHB1Periph_DMA1
#define UART_DRV_TX_DMA_CHAN DMA_Channel_4
#define UART_DRV_TX_DMA_IRQN DMA1_Stream6_IRQn
#define UART_DRV_TX_DMA_TCIF DMA_FLAG_TCIF6

#define UART_DRV_RX_PIN GPIO_Pin_3
#define UART_DRV_RX_PORT GPIOA
#define UART_DRV_RX_IO_RCC RCC_AHB1Periph_GPIOA
#define UART_DRV_RX_PIN_SOURCE GPIO_PinSource3
#define UART_DRV_RX_AF_SOURCE GPIO_AF_USART2

#define UART_DRV_TX_PIN GPIO_Pin_2
#define UART_DRV_TX_PORT GPIOA
#define UART_DRV_TX_IO_RCC RCC_AHB1Periph_GPIOA
#define UART_DRV_TX_PIN_SOURCE GPIO_PinSource2
#define UART_DRV_TX_AF_SOURCE GPIO_AF_USART2

#endif

// // i2c
// #define I2C I2C1
// #define I2C_RCC RCC_AHB1Periph_I2C1
//
// //// gpio
// #define I2C_SDA_PIN GPIO_Pin_9
// #define I2C_SDA_PORT GPIOB
// #define I2C_SDA_IO_RCC RCC_AHB1Periph_GPIOB
// #define I2C_SDA_PIN_SOURCE GPIO_PinSource9
// #define I2C_SDA_AF_SOURCE GPIO_AF_I2C1
//
// #define I2C_SCK_PIN GPIO_Pin_8
// #define I2C_SCK_PORT GPIOB
// #define I2C_SCK_IO_RCC RCC_AHB1Periph_GPIOB
// #define I2C_SCK_PIN_SOURCE GPIO_PinSource8
// #define I2C_SCK_AF_SOURCE GPIO_AF_I2C1
//
// // spi
// #define SPI SPI1
// #define SPI_RCC RCC_AHB1Periph_SPI1
//
// //// gpio
// #define SPI_MOSI_PIN GPIO_Pin_5
// #define SPI_MOSI_PORT GPIOB
// #define SPI_MOSI_IO_RCC RCC_AHB1Periph_GPIOB
// #define SPI_MOSI_PIN_SOURCE GPIO_PinSource5
// #define SPI_MOSI_AF_SOURCE GPIO_AF_SPI1
//
// #define SPI_MISO_PIN GPIO_Pin_4
// #define SPI_MISO_PORT GPIOB
// #define SPI_MISO_IO_RCC RCC_AHB1Periph_GPIOB
// #define SPI_MISO_PIN_SOURCE GPIO_PinSource4
// #define SPI_MISO_AF_SOURCE GPIO_AF_SPI1
//
// #define SPI_SCK_PIN GPIO_Pin_3
// #define SPI_SCK_PORT GPIOB
// #define SPI_SCK_IO_RCC RCC_AHB1Periph_GPIOB
// #define SPI_SCK_PIN_SOURCE GPIO_PinSource3
// #define SPI_SCK_AF_SOURCE GPIO_AF_SPI1
//
// // can
// #define CAN CAN1
// #define CAN_RCC RCC_AHB1Periph_CAN1
//
// //// gpio
// #define CAN_RX_PIN GPIO_Pin_8
// #define CAN_RX_PORT GPIOB
// #define CAN_RX_IO_RCC RCC_AHB1Periph_GPIOB
// #define CAN_RX_PIN_SOURCE GPIO_PinSource8
// #define CAN_RX_AF_SOURCE GPIO_AF_CAN1
//
// #define CAN_TX_PIN GPIO_Pin_9
// #define CAN_TX_PORT GPIOB
// #define CAN_TX_IO_RCC RCC_AHB1Periph_GPIOB
// #define CAN_TX_PIN_SOURCE GPIO_PinSource9
// #define CAN_TX_AF_SOURCE GPIO_AF_CAN1

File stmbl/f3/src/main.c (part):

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  MX_ADC3_Init();
  MX_ADC4_Init();
  MX_DAC_Init();
  //COMP1 in+ pa1(ADC1_IN2)  in- pa4(dac1_ch1)
  COMP1->CSR = COMP_CSR_COMPxINSEL_2 | COMP1_CSR_COMP1OUTSEL_2 | COMP_CSR_COMPxEN;
  //COMP2 in+ pa7(ADC2_IN4)  in- pa4(dac1_ch1) COMP_CSR_COMPxNONINSEL
  COMP2->CSR = COMP_CSR_COMPxINSEL_2 | COMP2_CSR_COMP2OUTSEL_0 | COMP2_CSR_COMP2OUTSEL_1 | COMP_CSR_COMPxEN;
  //COMP4 in+ pb0(ADC3_IN12) in- pa4(dac1_ch1)
  COMP4->CSR = COMP_CSR_COMPxINSEL_2 | COMP4_CSR_COMP4OUTSEL_0 | COMP4_CSR_COMP4OUTSEL_1 | COMP_CSR_COMPxEN;
  MX_OPAMP1_Init();
  MX_OPAMP2_Init();
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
